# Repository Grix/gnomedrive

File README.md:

# gnomedrive

experimental ultra low dropout laser diode linear driver

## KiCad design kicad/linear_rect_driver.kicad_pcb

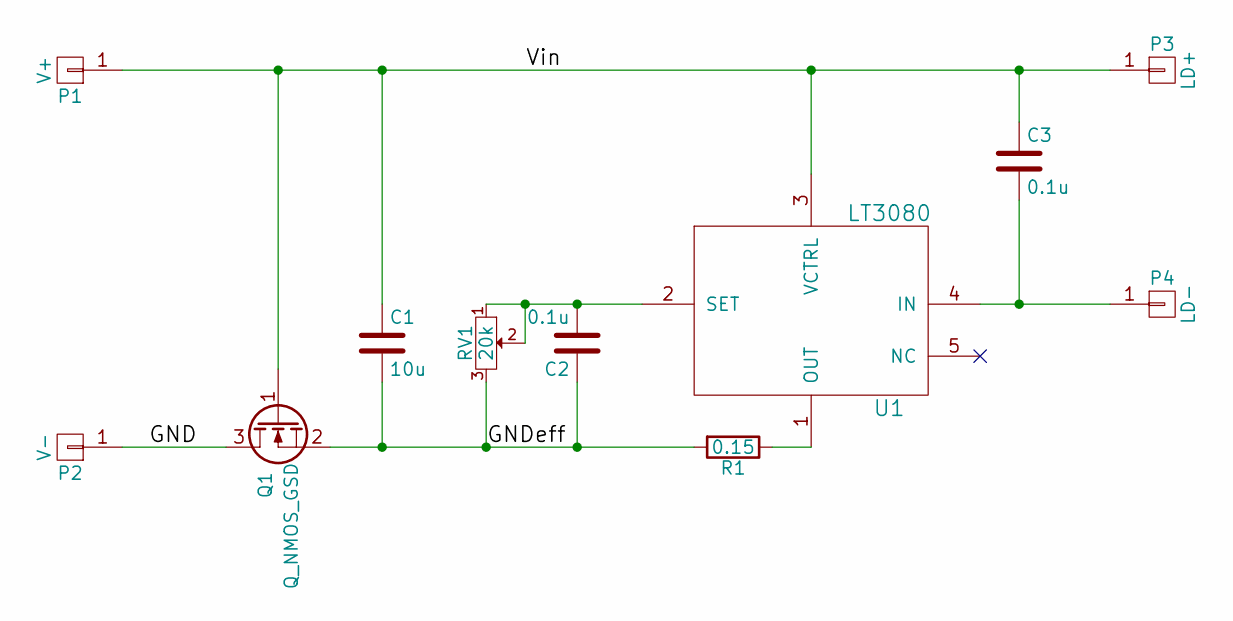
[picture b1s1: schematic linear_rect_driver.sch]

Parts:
C1: 10u; C_1206; PartNumber CL31B106KAHNNNE
C2, C3: 0.1u; C_0402
P1: V+; LDpad
P2: V-; LDpad
P3: LD+; LDpad
P4: LD-; LDpad
Q1: Q_NMOS_GSD; SOT-23; PartNumber DMN3404L-7
R1: 0.15; R_1210; PartNumber MCR25JZHFLR150
RV1: 20k; POT-TC33; PartNumber TC33X-2-203E
U1: LT3080; DFN8-LT3080

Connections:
/GND: P2.1, Q1.3 (D)
/GNDeff: C1.2, C2.1, Q1.2 (S), R1.2, RV1.3
/Vin: C1.1, C3.1, P1.1, P3.1, Q1.1 (G), U1.3 (VCTRL)
unnamed: C2.2, RV1.1, RV1.2, U1.2 (SET)
unnamed: C3.2, P4.1, U1.4 (IN)
unnamed: R1.1, U1.1 (OUT)

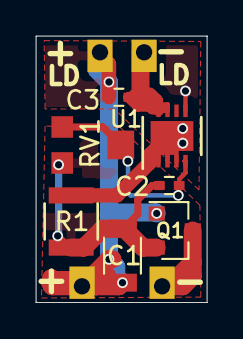
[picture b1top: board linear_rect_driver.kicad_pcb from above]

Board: 2 copper layers, 9.5 x 14.8 mm, 11 parts (0 on the bottom side), 6 nets.

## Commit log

2017-02-17 add kicad project
2017-02-17 metafiles
2017-02-20 misc pcb changes
